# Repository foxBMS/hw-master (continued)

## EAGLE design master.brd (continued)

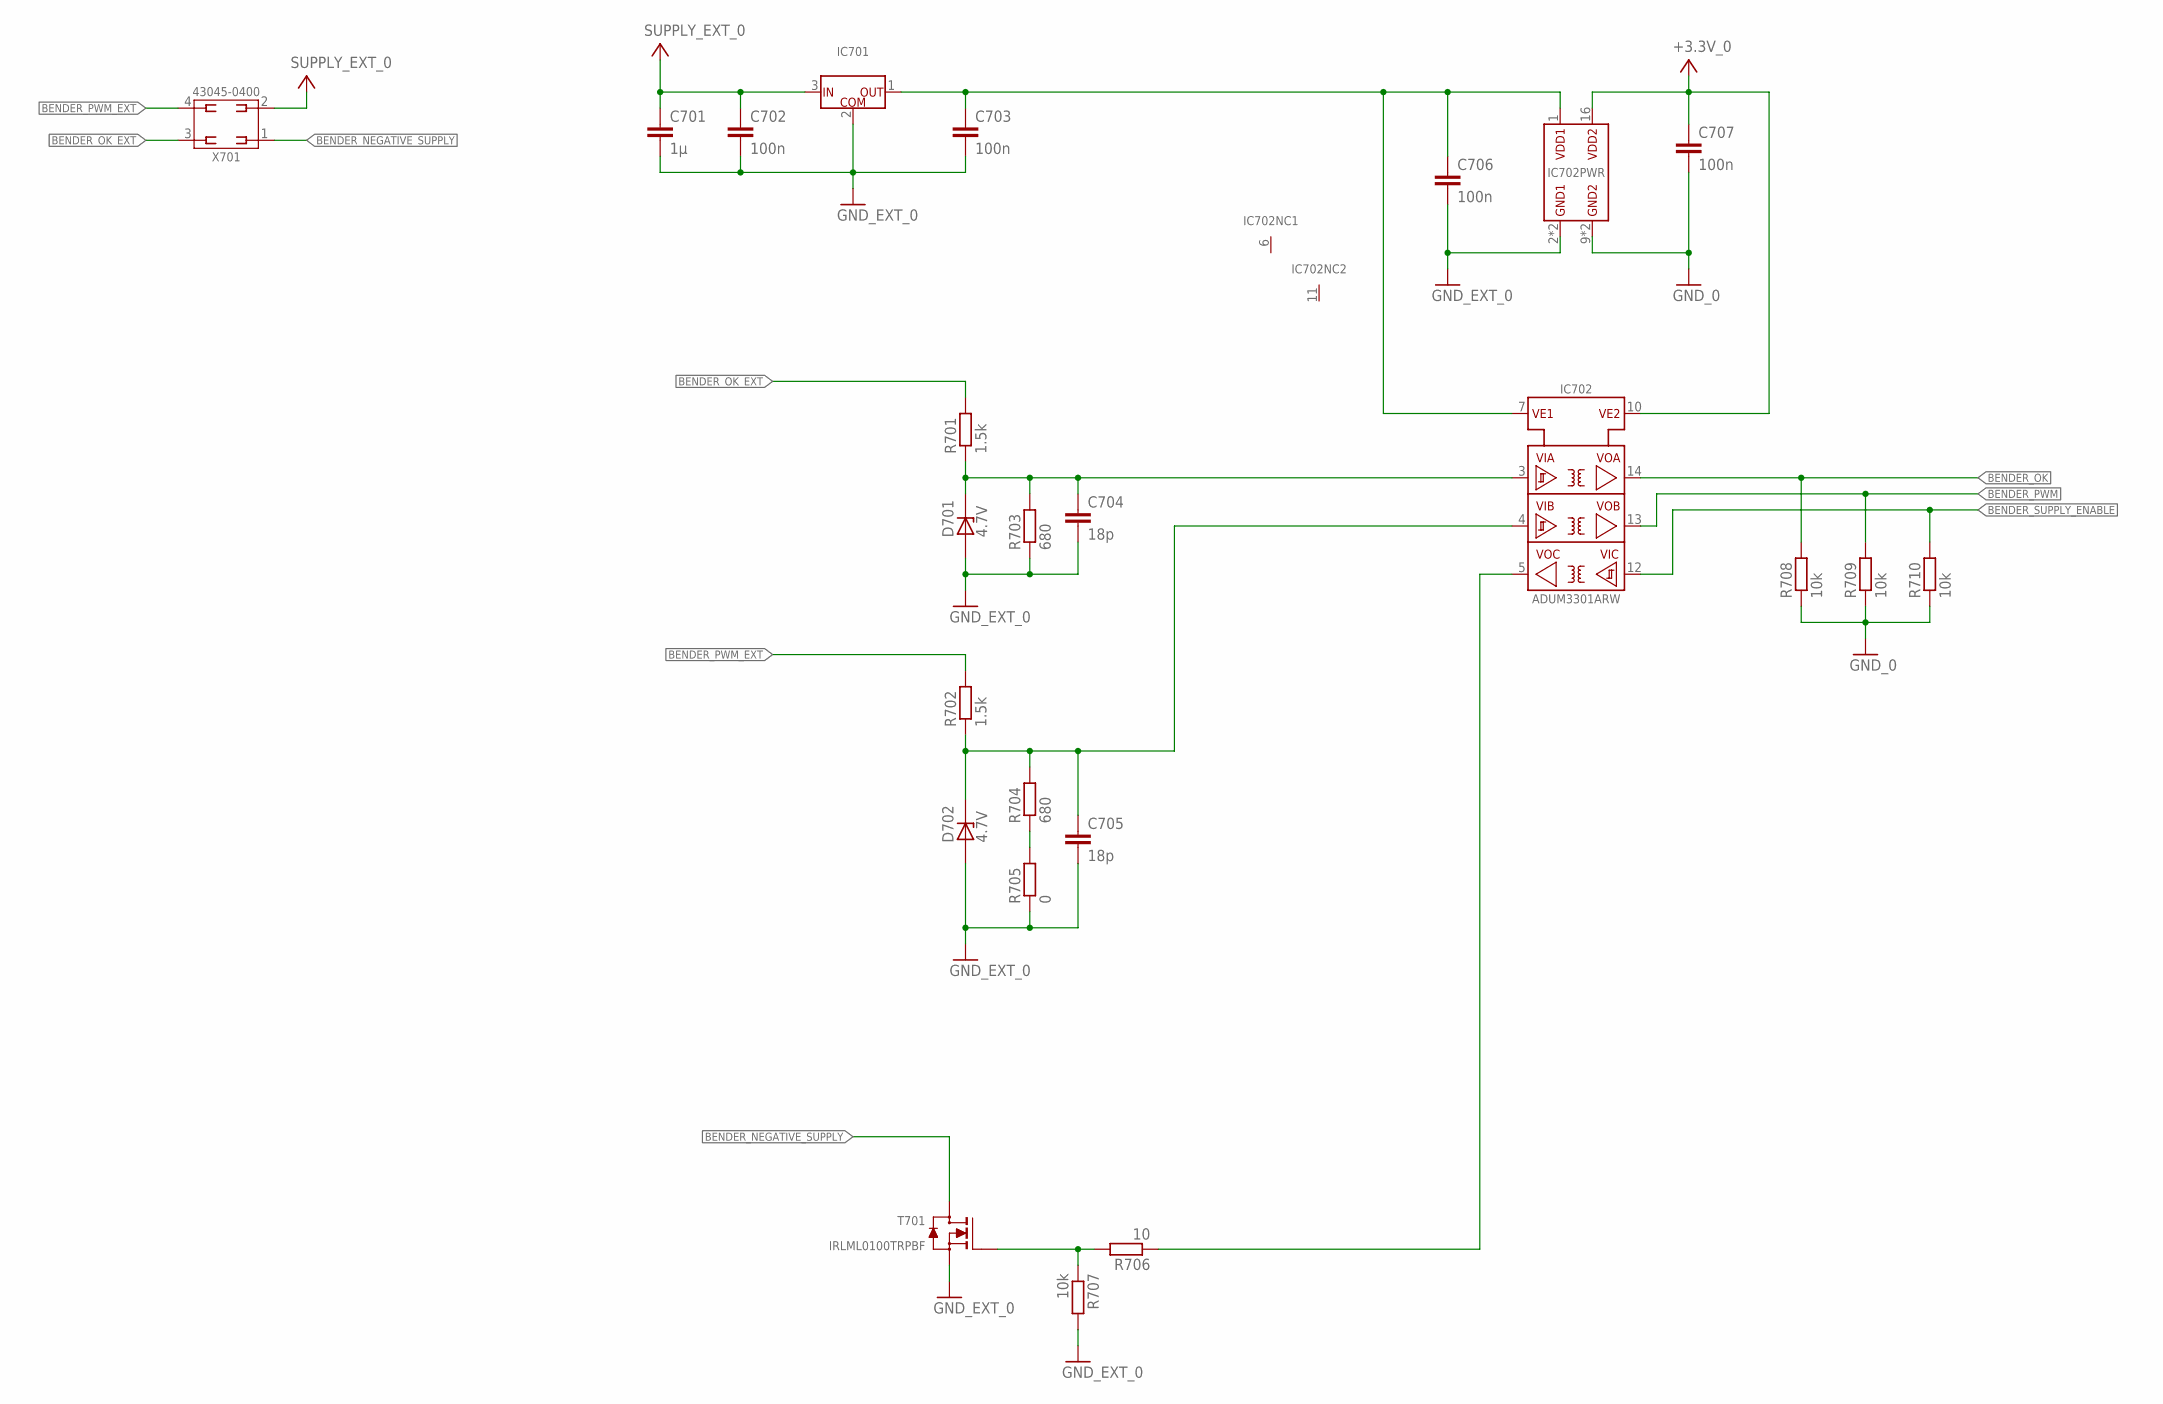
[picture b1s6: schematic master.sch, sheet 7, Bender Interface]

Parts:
C701: 1µ; C0603
C702, C703, C706, C707: 100n; C0603
C704, C705: 18p; C0603
D701, D702: 4.7V; SOD323
IC701: UA78L05ACPK; IC_SMD_SOT-89_(SC-62/TO-243)_(R-PSSO-F3)_R_TI_REV01
IC702: ADUM3301ARW; IC_SMD_SOIC-16_(JEDEC_MS-013-AA)_R_ANALOG_REV01
R701, R702: 1.5k; R0603
R703, R704: 680; R0603
R705: 0; R0603
R706: 10; R0603
R707, R708, R709, R710: 10k; R0603
T701: IRLML0100TRPBF; V_SMD_SOT-23_(TO-236AB)_R_IR_REV01
X701: 43045-0400_MOLEX_4PIN; X_TH_MOLEX_43045-0400_R_REV01

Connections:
+3.3V_0: C707.1, IC702.10 (VE2), IC702.16 (VDD2); also elsewhere on the board
BENDER_ADUM_SUPPLY: C703.1, C706.1, IC701.1 (OUT), IC702.1 (VDD1), IC702.7 (VE1)
BENDER_NEGATIVE_SUPPLY: T701.3 (D), X701.1
BENDER_OK: IC702.14 (VOA), R708.2; also elsewhere on the board
BENDER_OK_EXT: R701.2, X701.3
BENDER_PWM: IC702.13 (VOB), R709.2; also elsewhere on the board
BENDER_PWM_EXT: R702.2, X701.4
BENDER_SUPPLY_ENABLE: IC702.12 (VIC), R710.2; also elsewhere on the board
GND_0: C707.2, IC702.9 (GND2), IC702.15 (GND2), R708.1, R709.1, R710.1; also elsewhere on the board
GND_EXT_0: C701.2, C702.2, C703.2, C704.2, C705.2, C706.2, D701.A, D702.A, IC701.2 (COM), IC702.2 (GND1), IC702.8 (GND1), R703.1, R705.1, R707.2, T701.2 (S); also elsewhere on the board
unnamed: IC702.5 (VOC), R706.1
unnamed: R706.2, R707.1, T701.1 (G)
unnamed: C705.1, D702.C (K), IC702.4 (VIB), R702.1, R704.2
unnamed: C704.1, D701.C (K), IC702.3 (VIA), R701.1, R703.2
unnamed: R704.1, R705.2
SUPPLY_EXT_0: C701.1, C702.1, IC701.3 (IN), X701.2; also elsewhere on the board

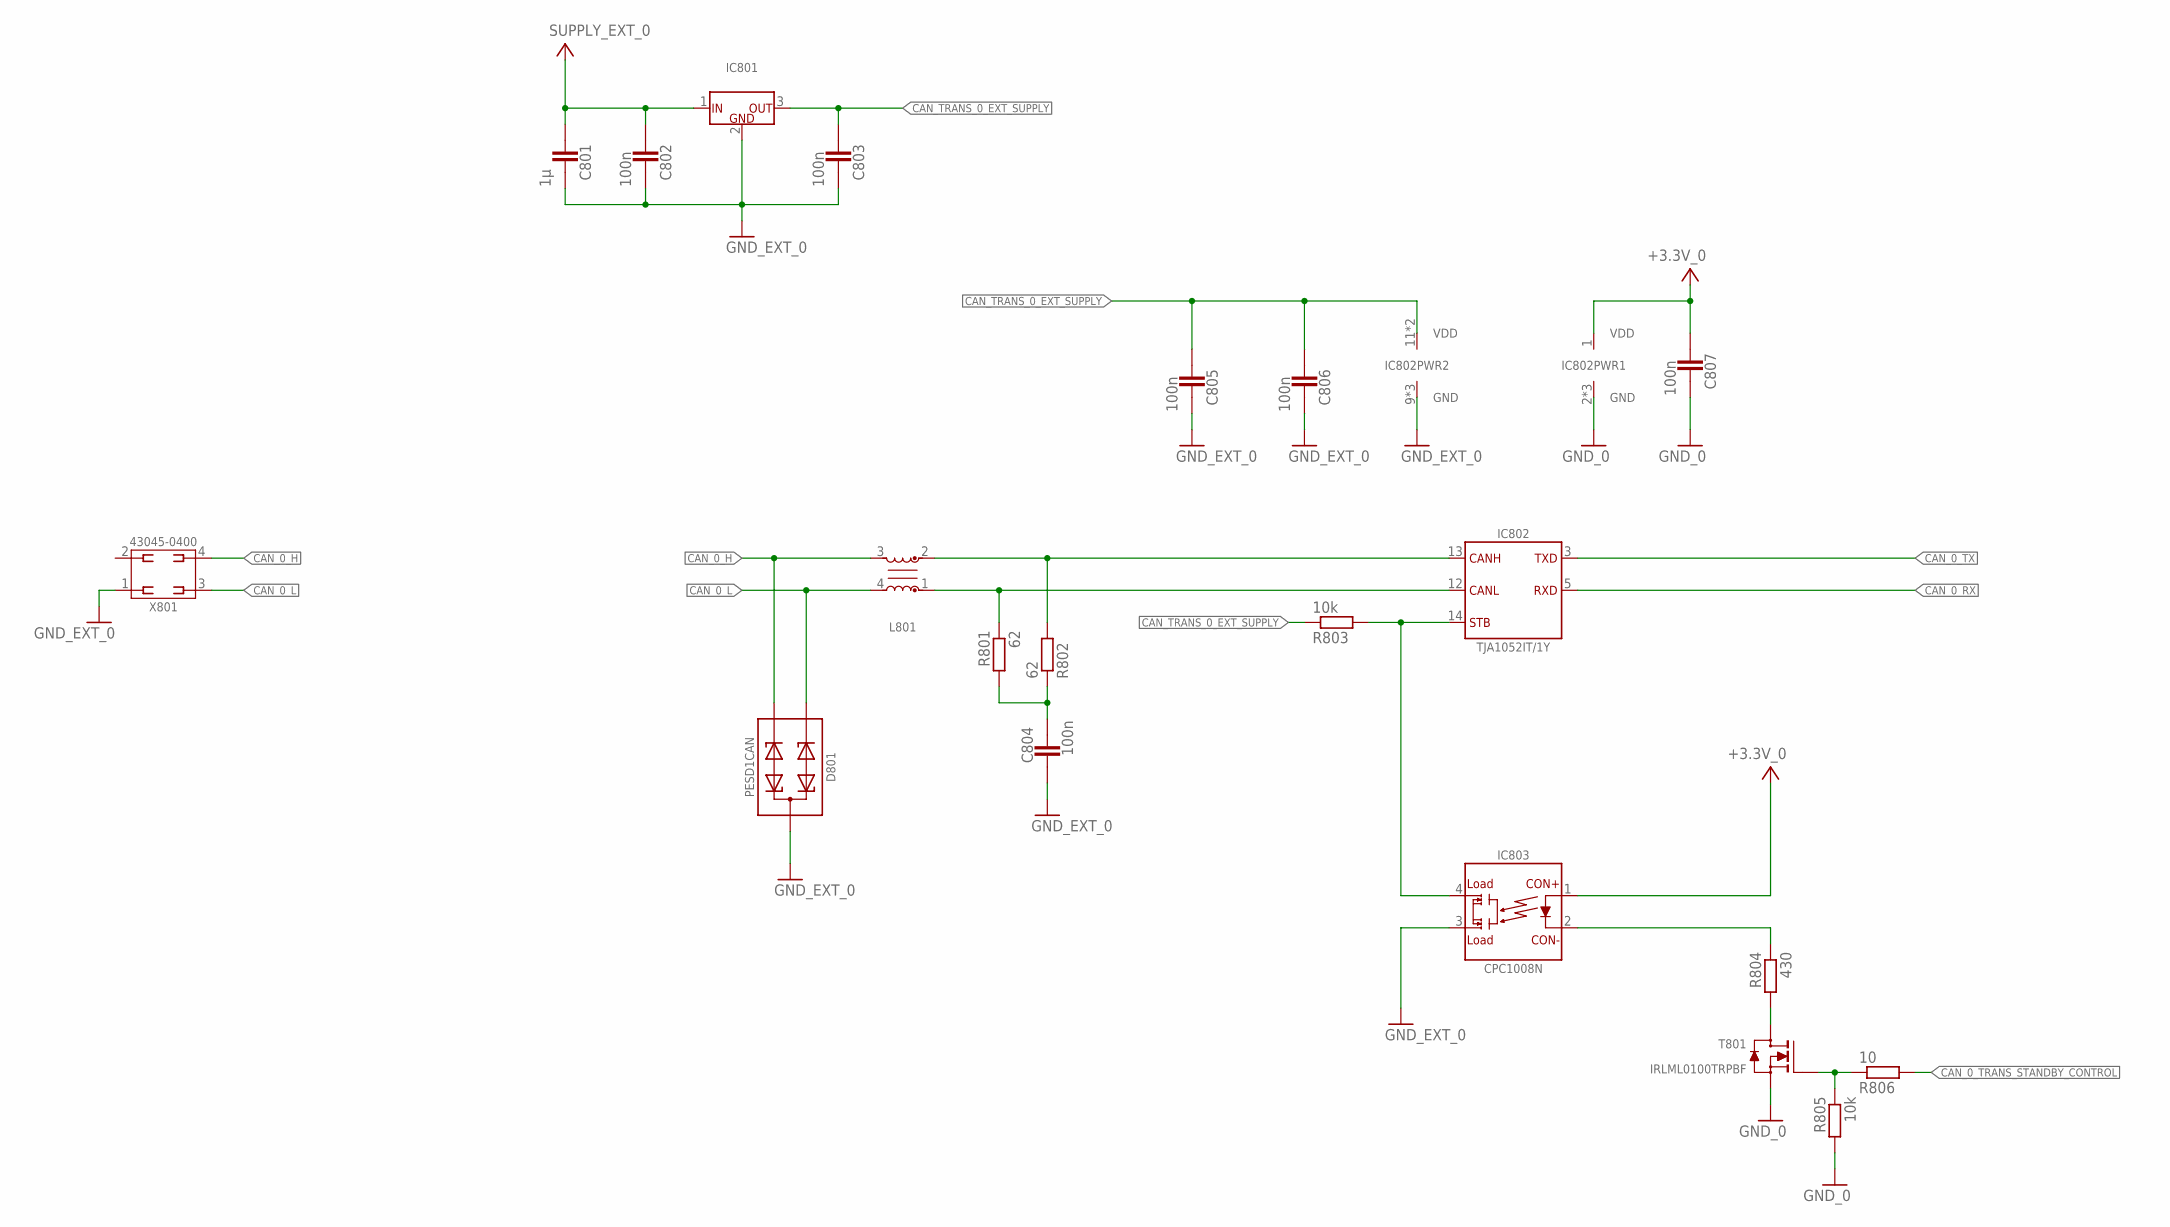
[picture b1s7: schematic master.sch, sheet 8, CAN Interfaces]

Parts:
C801: 1µ; 0603
C802, C803, C804, C805, C806, C807: 100n; 0603
D801: PESD1CAN; D_SMD_SOT23_(TO-236AB)_R_NXP_REV01
IC801: KA7805ERTF; IC_SMD_TO-252_(D-PAK)_R_FAIRCHILD_REV01
IC802: TJA1052IT/1Y; IC_SMD_SO16_(SOT162-1)_R_NXP_REV01
IC803: CPC1008N; K_SMD_SOP-4_R_IXYS_REV01
L801: B82789C0513H001; L_SMD_FILTER_HF_R_EPCOS_SIMDAD_1812_REV01
R801, R802: 62; R0603
R803, R805: 10k; 0603
R804: 430; 0603
R806: 10; 0603
T801: IRLML0100TRPBF; V_SMD_SOT-23_(TO-236AB)_R_IR_REV01
X801: 43045-0400_MOLEX_4PIN; X_TH_MOLEX_43045-0400_R_REV01

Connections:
+3.3V_0: C807.2, IC802.1 (VDD), IC803.1 (CON+); also elsewhere on the board
CAN_0_H: D801.2, L801.3, X801.4
CAN_0_L: D801.1, L801.4, X801.3
CAN_0_RX: IC802.5 (RXD); also elsewhere on the board
CAN_0_TRANS_STANDBY_CONTROL: R806.2; also elsewhere on the board
CAN_0_TX: IC802.3 (TXD); also elsewhere on the board
CAN_L_INT: IC802.12 (CANL), L801.1, R801.1
CAN_SPLIT: C804.1, R801.2, R802.1
CAN_TRANS_0_EXT_SUPPLY: C803.2, C805.2, C806.2, IC801.3 (OUT), IC802.11 (VDD), IC802.16 (VDD), R803.1
CAN_TRANS_0_STANDBY: IC802.14 (STB), IC803.4, R803.2
GND_0: C807.1, IC802.2 (GND), IC802.7 (GND), IC802.8 (GND), R805.2, T801.2 (S); also elsewhere on the board
GND_EXT_0: C801.1, C802.1, C803.1, C804.2, C805.1, C806.1, D801.3, IC801.2 (GND), IC802.9 (GND), IC802.10 (GND), IC802.15 (GND), IC803.3, X801.1; also elsewhere on the board
unnamed: R804.2, T801.3 (D)
unnamed: IC802.13 (CANH), L801.2, R802.2
unnamed: IC803.2 (CON-), R804.1
unnamed: R805.1, R806.1, T801.1 (G)
SUPPLY_EXT_0: C801.2, C802.2, IC801.1 (IN); also elsewhere on the board

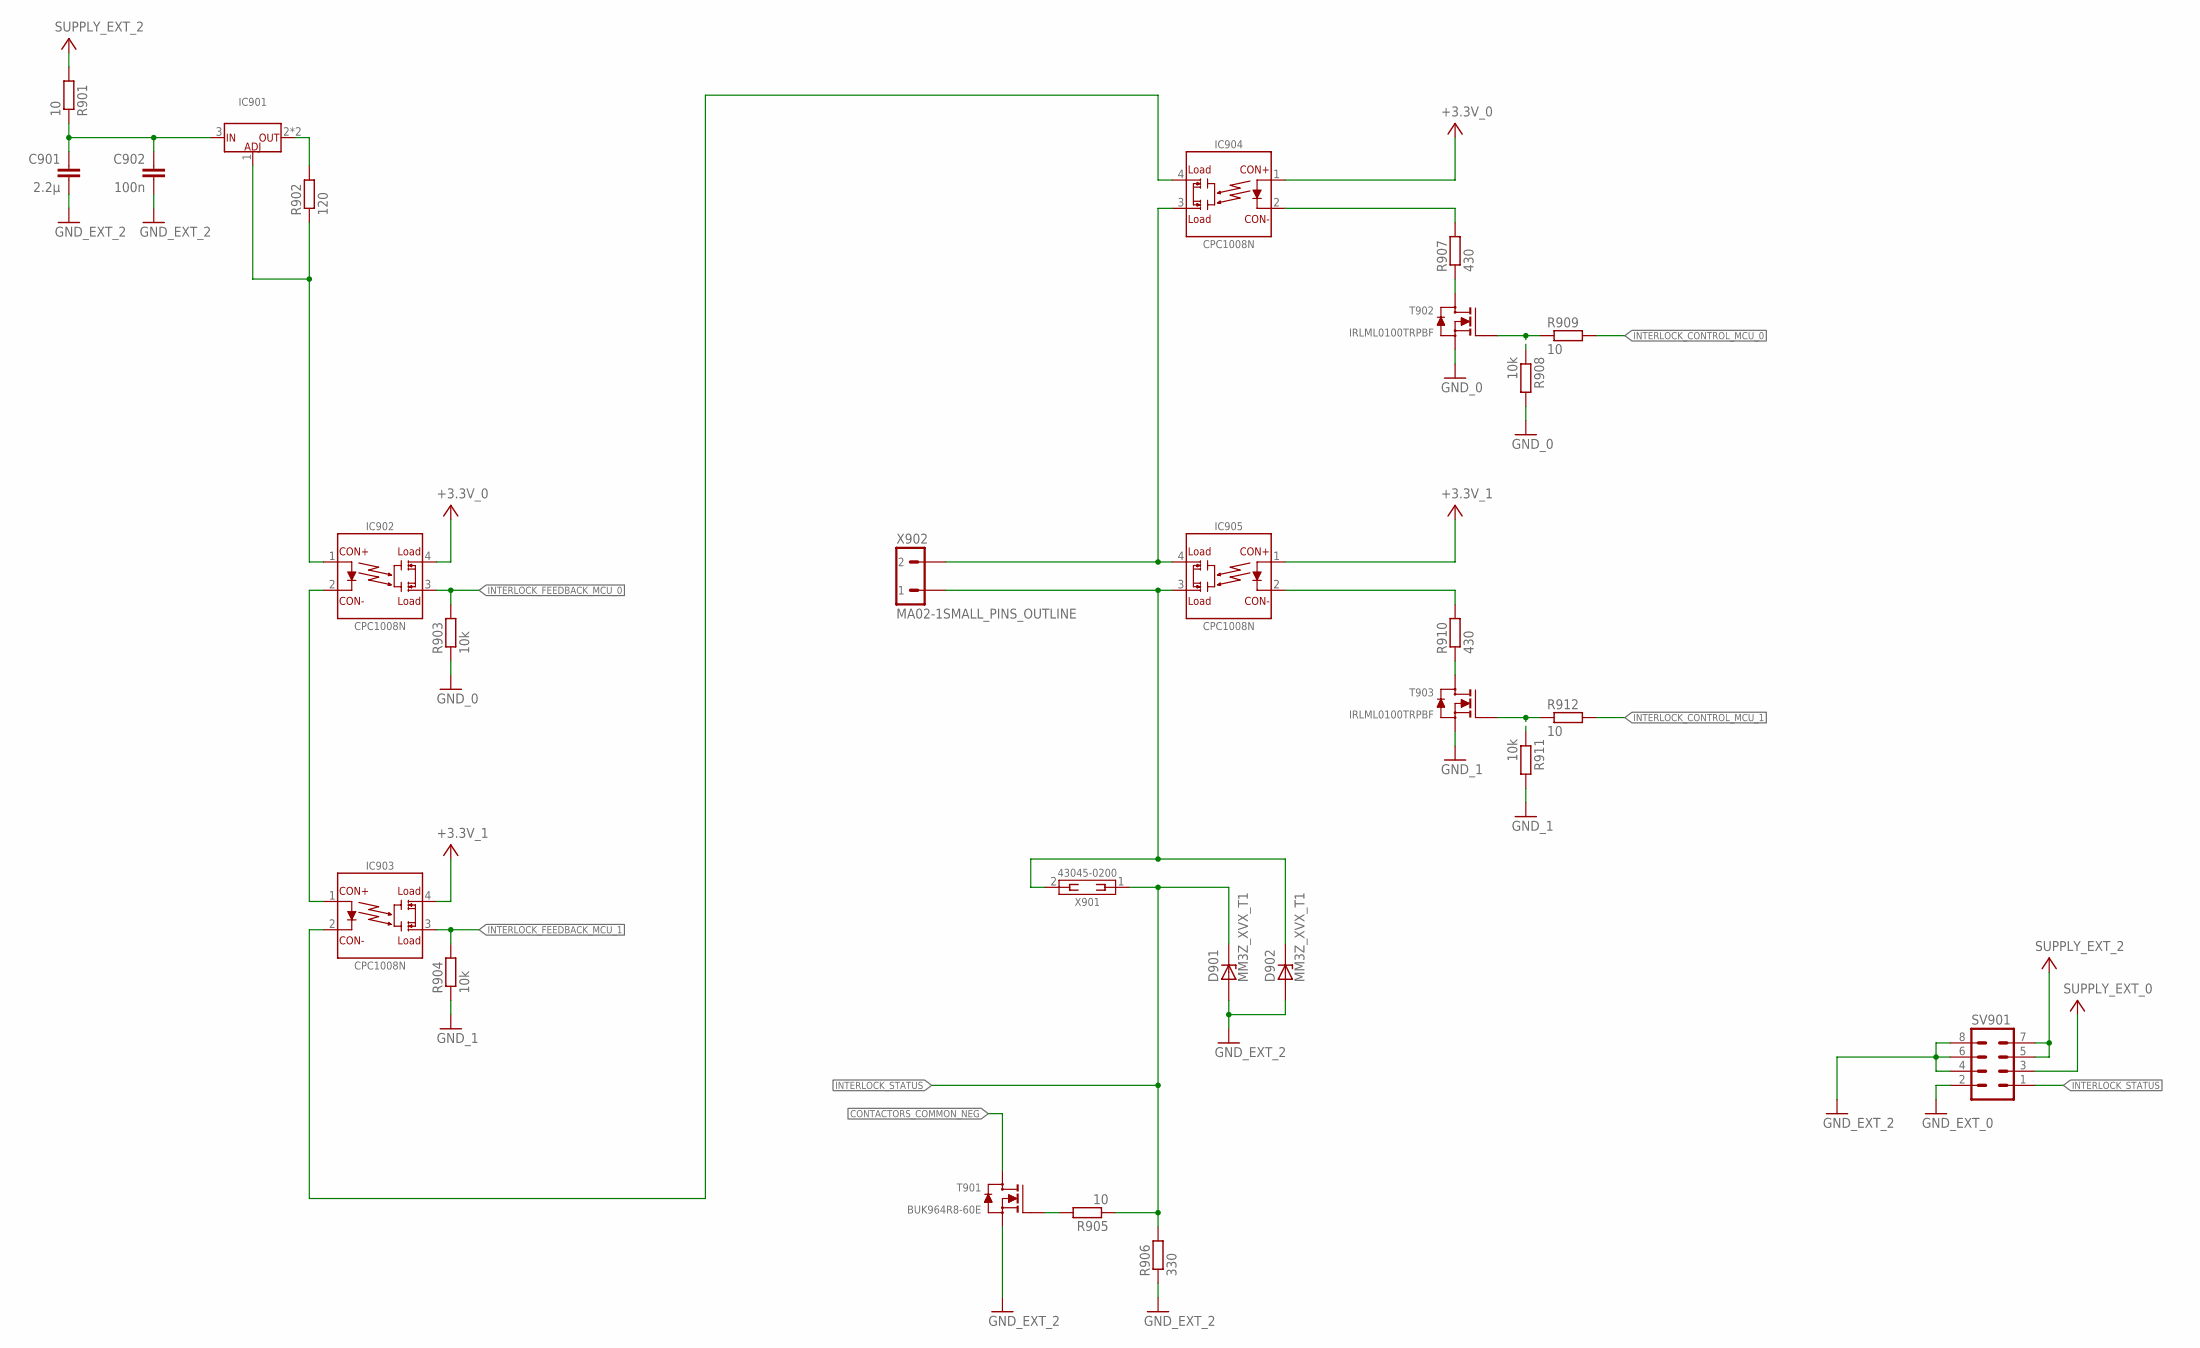
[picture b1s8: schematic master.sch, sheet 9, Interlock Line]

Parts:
C901: 2.2µ; C0805
C902: 100n; C0603
D901, D902: MM3Z_XVX_T1; SOD323
IC901: LM317MBSTT3G; IC_SMD_SOT-223_(TO-261)_(CASE318E-04)_R_REV01
IC902, IC903, IC904, IC905: CPC1008N; K_SMD_SOP-4_R_IXYS_REV01
R901, R905, R909, R912: 10; R0603
R902: 120; R0603
R903, R904, R908, R911: 10k; R0603
R906: 330; R0603
R907, R910: 430; R0603
SV901: MA04-2
T901: BUK964R8-60E; V_SMD_TO-263_(D²PAK)_R_NXP_REV01
T902, T903: IRLML0100TRPBF; V_SMD_SOT-23_(TO-236AB)_R_IR_REV01
X901: 43045-0200_MOLEX_2PIN; X_TH_MOLEX_43045-0200_R_REV01
X902: MA02-1SMALL_PINS_OUTLINE; MA02-1A

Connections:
+3.3V_0: IC902.4, IC904.1 (CON+); also elsewhere on the board
+3.3V_1: IC903.4, IC905.1 (CON+); also elsewhere on the board
CONTACTORS_COMMON_NEG: T901.2 (D); also elsewhere on the board
GND_0: R903.1, R908.2, T902.2 (S); also elsewhere on the board
GND_1: R904.1, R911.2, T903.2 (S); also elsewhere on the board
GND_EXT_0: SV901.2; also elsewhere on the board
GND_EXT_2: C901.2, C902.2, D901.A, D902.A, R906.1, SV901.4, SV901.6, SV901.8, T901.3 (S); also elsewhere on the board
INTERLOCK_CONTROL_MCU_0: R909.2; also elsewhere on the board
INTERLOCK_CONTROL_MCU_1: R912.2; also elsewhere on the board
INTERLOCK_FEEDBACK_MCU_0: IC902.3, R903.2; also elsewhere on the board
INTERLOCK_FEEDBACK_MCU_1: IC903.3, R904.2; also elsewhere on the board
INTERLOCK_STATUS: D901.C (K), R905.1, R906.2, SV901.1, X901.1
unnamed: R905.2, T901.1 (G)
unnamed: D902.C (K), IC905.3, X901.2, X902.1
unnamed: R907.1, T902.3 (D)
unnamed: R910.1, T903.3 (D)
unnamed: C901.1, C902.1, IC901.3 (IN), R901.1
unnamed: IC901.2 (OUT), IC901.4 (OUT), R902.2
unnamed: IC901.1 (ADJ), IC902.1 (CON+), R902.1
unnamed: IC902.2 (CON-), IC903.1 (CON+)
unnamed: IC905.2 (CON-), R910.2
unnamed: R911.1, R912.1, T903.1 (G)
unnamed: IC903.2 (CON-), IC904.4
unnamed: IC904.2 (CON-), R907.2
unnamed: R908.1, R909.1, T902.1 (G)
unnamed: IC904.3, IC905.4, X902.2
SUPPLY_EXT_0: SV901.3; also elsewhere on the board
SUPPLY_EXT_2: R901.2, SV901.5, SV901.7; also elsewhere on the board

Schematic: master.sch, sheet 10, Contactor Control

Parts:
D1001, D1002, D1003, D1004, D1005, D1006: GF1; SMA-DO214AC
F1001, F1002, F1003, F1004, F1005, F1006: 4,00A_UMT; F_SMD_11,00MMX3,00MMX3,00MM_(UMT)_R_SCHURTER_REV01
IC1001, IC1002, IC1003, IC1004, IC1005, IC1006: AQV252G2S; K_SMD_SOP-6_R_PANASONIC_REV01
R1001, R1002, R1007, R1008, R1013, R1014: 10; R0603
R1003, R1004, R1009, R1010, R1015, R1016: 10k; R0603
R1005, R1006, R1011, R1012, R1017, R1018: 430; R0603
T1001, T1002, T1003, T1004, T1005, T1006: IRLML0100TRPBF; V_SMD_SOT-23_(TO-236AB)_R_IR_REV01

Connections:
+3.3V_0: IC1001.1, IC1002.1, IC1003.1, IC1004.1, IC1005.1, IC1006.1; also elsewhere on the board
CONTACTORS_COMMON_NEG: D1001.A, D1002.A, D1003.A, D1004.A, D1005.A, D1006.A; also elsewhere on the board
CONTACTOR_0_COIL_POS: D1001.K (C), F1001.2; also elsewhere on the board
CONTACTOR_0_CONTROL: R1001.2; also elsewhere on the board
CONTACTOR_1_COIL_POS: D1003.K (C), F1003.2; also elsewhere on the board
CONTACTOR_1_CONTROL: R1007.2; also elsewhere on the board
CONTACTOR_2_COIL_POS: D1005.K (C), F1005.2; also elsewhere on the board
CONTACTOR_2_CONTROL: R1013.2; also elsewhere on the board
CONTACTOR_3_COIL_POS: D1002.K (C), F1002.2; also elsewhere on the board
CONTACTOR_3_CONTROL: R1002.2; also elsewhere on the board
CONTACTOR_4_COIL_POS: D1004.K (C), F1004.2; also elsewhere on the board
CONTACTOR_4_CONTROL: R1008.2; also elsewhere on the board
CONTACTOR_5_COIL_POS: D1006.K (C), F1006.2; also elsewhere on the board
CONTACTOR_5_CONTROL: R1014.2; also elsewhere on the board
GND_0: R1003.1, R1004.1, R1009.1, R1010.1, R1015.1, R1016.1, T1001.2 (S), T1002.2 (S), T1003.2 (S), T1004.2 (S), T1005.2 (S), T1006.2 (S); also elsewhere on the board
unnamed: IC1002.2, R1006.2
unnamed: R1006.1, T1002.3 (D)
unnamed: IC1001.2, R1005.2
unnamed: R1005.1, T1001.3 (D)
unnamed: R1011.1, T1003.3 (D)
unnamed: IC1003.2, R1011.2
unnamed: IC1004.2, R1012.2
unnamed: R1012.1, T1004.3 (D)
unnamed: IC1005.2, R1017.2
unnamed: R1017.1, T1005.3 (D)
unnamed: IC1006.2, R1018.2
unnamed: R1018.1, T1006.3 (D)
unnamed: F1001.1, IC1001.5
unnamed: F1003.1, IC1003.5
unnamed: F1004.1, IC1004.5
unnamed: F1005.1, IC1005.5
unnamed: F1002.1, IC1002.5
unnamed: F1006.1, IC1006.5
unnamed: R1007.1, R1009.2, T1003.1 (G)
unnamed: R1001.1, R1003.2, T1001.1 (G)
unnamed: R1013.1, R1015.2, T1005.1 (G)
unnamed: R1002.1, R1004.2, T1002.1 (G)
unnamed: R1008.1, R1010.2, T1004.1 (G)
unnamed: R1014.1, R1016.2, T1006.1 (G)
SUPPLY_EXT_2: IC1001.4, IC1001.6, IC1002.4, IC1002.6, IC1003.4, IC1003.6, IC1004.4, IC1004.6, IC1005.4, IC1005.6, IC1006.4, IC1006.6; also elsewhere on the board

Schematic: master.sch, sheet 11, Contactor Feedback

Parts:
C1101: 1µ; C0603
C1102, C1103, C1104, C1105, C1106, C1107: 100n; C0603
D1101, D1102, D1103, D1104, D1105, D1106: CDSOD323-T05; D_SMD_SOD323_(SC-76)_R_BOURNS_REV01
IC1101: UA78L05ACPK; IC_SMD_SOT-89_(SC-62/TO-243)_(R-PSSO-F3)_R_TI_REV01
IC1102, IC1103: ADUM3300ARW; IC_SMD_SOIC-16_(JEDEC_MS-013-AA)_R_ANALOG_REV01
R1101, R1102, R1103, R1104, R1105, R1106: 47; R0603
R1107, R1108, R1109, R1110, R1111, R1112: 10k; R0603

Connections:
+3.3V_0: C1106.1, C1107.1, IC1102.10 (VE2), IC1102.16 (VDD2), IC1103.10 (VE2), IC1103.16 (VDD2); also elsewhere on the board
CONTACTOR_0_FEEDBACK: IC1102.14 (VOA); also elsewhere on the board
CONTACTOR_0_FEEDBACK_EXT: R1101.1; also elsewhere on the board
CONTACTOR_1_FEEDBACK: IC1102.13 (VOB); also elsewhere on the board
CONTACTOR_1_FEEDBACK_EXT: R1102.1; also elsewhere on the board
CONTACTOR_2_FEEDBACK: IC1102.12 (VOC); also elsewhere on the board
CONTACTOR_2_FEEDBACK_EXT: R1103.1; also elsewhere on the board
CONTACTOR_3_FEEDBACK: IC1103.14 (VOA); also elsewhere on the board
CONTACTOR_3_FEEDBACK_EXT: R1104.2; also elsewhere on the board
CONTACTOR_4_FEEDBACK: IC1103.13 (VOB); also elsewhere on the board
CONTACTOR_4_FEEDBACK_EXT: R1105.2; also elsewhere on the board
CONTACTOR_5_FEEDBACK: IC1103.12 (VOC); also elsewhere on the board
CONTACTOR_5_FEEDBACK_EXT: R1106.2; also elsewhere on the board
CONTACTOR_FEEDBACK_SUPPLY_EXT: C1103.1, C1104.1, C1105.1, IC1101.1 (OUT), IC1102.1 (VDD1), IC1103.1 (VDD1), R1107.2, R1108.2, R1109.2, R1110.2, R1111.2, R1112.2
GND_0: C1106.2, C1107.2, IC1102.9 (GND2), IC1102.15 (GND2), IC1103.9 (GND2), IC1103.15 (GND2); also elsewhere on the board
GND_EXT_0: C1101.2, C1102.2, C1103.2, C1104.2, C1105.2, D1101.A, D1102.A, D1103.A, D1104.A, D1105.A, D1106.A, IC1101.2 (COM), IC1102.2 (GND1), IC1102.8 (GND1), IC1103.2 (GND1), IC1103.8 (GND1); also elsewhere on the board
unnamed: D1101.C, IC1102.3 (VIA), R1101.2, R1107.1
unnamed: D1103.C, IC1102.4 (VIB), R1102.2, R1109.1
unnamed: D1105.C, IC1102.5 (VIC), R1103.2, R1111.1
unnamed: D1102.C, IC1103.3 (VIA), R1104.1, R1108.1
unnamed: D1104.C, IC1103.4 (VIB), R1105.1, R1110.1
unnamed: D1106.C, IC1103.5 (VIC), R1106.1, R1112.1
SUPPLY_EXT_0: C1101.1, C1102.1, IC1101.3 (IN); also elsewhere on the board

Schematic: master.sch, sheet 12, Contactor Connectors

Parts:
X1201, X1202, X1203, X1204, X1205, X1206: 43045-0400_MOLEX_4PIN; X_TH_MOLEX_43045-0400_R_REV01

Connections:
CONTACTORS_COMMON_NEG: X1201.4, X1202.4, X1203.4, X1204.4, X1205.4, X1206.4; also elsewhere on the board
CONTACTOR_0_COIL_POS: X1201.3; also elsewhere on the board
CONTACTOR_0_FEEDBACK_EXT: X1201.2; also elsewhere on the board
CONTACTOR_1_COIL_POS: X1203.3; also elsewhere on the board
CONTACTOR_1_FEEDBACK_EXT: X1203.2; also elsewhere on the board
CONTACTOR_2_COIL_POS: X1205.3; also elsewhere on the board
CONTACTOR_2_FEEDBACK_EXT: X1205.2; also elsewhere on the board
CONTACTOR_3_COIL_POS: X1202.3; also elsewhere on the board
CONTACTOR_3_FEEDBACK_EXT: X1202.2; also elsewhere on the board
CONTACTOR_4_COIL_POS: X1204.3; also elsewhere on the board
CONTACTOR_4_FEEDBACK_EXT: X1204.2; also elsewhere on the board
CONTACTOR_5_COIL_POS: X1206.3; also elsewhere on the board
CONTACTOR_5_FEEDBACK_EXT: X1206.2; also elsewhere on the board
GND_EXT_0: X1201.1, X1202.1, X1203.1, X1204.1, X1205.1, X1206.1; also elsewhere on the board

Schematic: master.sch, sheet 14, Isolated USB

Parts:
C1401, C1406: 4.7µ; C0603
C1402, C1403, C1404, C1405, C1407, C1408, C1409, C1410: 100n; C0603
IC1401, IC1404: IP4220CZ6; D_SMD_TSOP6_(SOT457/SC-74)_R_NXP_REV01
IC1402, IC1405: FT231XS-R; IC_SMD_SSOP-20_R_FTDI_REV01
IC1403, IC1406: ADUM3401ARW; IC_SMD_SOIC-16_(JEDEC_MS-013-AA)_R_ANALOG_REV01
R1401, R1402, R1405, R1406: 27; 0603
R1403, R1404, R1407, R1408: 0; 0603
X1401, X1402: MINI-USB-2.0; X_SMD_MINI-USB-2.0-TYPAB_R_MULTICOMP_REV01

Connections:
+3.3V_0: C1405.1, IC1403.10 (VE2), IC1403.16 (VDD2); also elsewhere on the board
+3.3V_1: C1410.1, IC1406.10 (VE2), IC1406.16 (VDD2); also elsewhere on the board
DM: IC1401.4 (I/O3), R1401.2, X1401.2
DM1: IC1404.4 (I/O3), R1405.2, X1402.2
DP: IC1401.6 (I/O4), R1402.2, X1401.3
DP1: IC1404.6 (I/O4), R1406.2, X1402.3
FTDI_MCU_0_DTR: IC1403.13 (VOB); also elsewhere on the board
FTDI_MCU_0_RTS: IC1403.14 (VOA); also elsewhere on the board
FTDI_MCU_0_RX: IC1403.12 (VOC); also elsewhere on the board
FTDI_MCU_0_TX: IC1403.11 (VID); also elsewhere on the board
FTDI_MCU_1_DTR: IC1406.13 (VOB); also elsewhere on the board
FTDI_MCU_1_RTS: IC1406.14 (VOA); also elsewhere on the board
FTDI_MCU_1_RX: IC1406.12 (VOC); also elsewhere on the board
FTDI_MCU_1_TX: IC1406.11 (VID); also elsewhere on the board
GND_0: C1405.2, IC1403.9 (GND2), IC1403.15 (GND2); also elsewhere on the board
GND_1: C1410.2, IC1406.9 (GND2), IC1406.15 (GND2); also elsewhere on the board
unnamed: IC1402.11 (USBDP), R1402.1
unnamed: IC1402.12 (USBDM), R1401.1
unnamed: IC1405.11 (USBDP), R1406.1
unnamed: IC1405.12 (USBDM), R1405.1
unnamed: IC1402.20 (TXD), IC1403.5 (VIC)
unnamed: IC1405.20 (TXD), IC1406.5 (VIC)
unnamed: IC1405.4 (RXD), IC1406.6 (VOD)
unnamed: IC1405.2 (RTS#), IC1406.3 (VIA)
unnamed: IC1405.1 (DTR#), IC1406.4 (VIB)
unnamed: IC1402.4 (RXD), IC1403.6 (VOD)
unnamed: IC1402.1 (DTR#), IC1403.4 (VIB)
unnamed: C1409.1, IC1405.3 (VCCIO), IC1405.13 (3V3OUT), IC1405.14 (RESET#)
unnamed: IC1405.9 (CTS#), R1407.1
unnamed: IC1402.2 (RTS#), IC1403.3 (VIA)
unnamed: IC1405.7 (DSR#), R1408.1
unnamed: IC1402.9 (CTS#), R1403.1
unnamed: IC1402.7 (DSR#), R1404.1
USB_0_GND_EXT: C1401.2, C1402.2, C1403.2, C1404.2, IC1401.2 (GND), IC1402.6 (GND1), IC1402.16 (GND2), IC1403.2 (GND1), IC1403.8 (GND1), R1403.2, R1404.2, X1401.5
USB_0_VBUS1_EXT: C1401.1, C1402.1, C1403.1, IC1401.5 (VP), IC1402.15 (VCC), IC1403.1 (VDD1), IC1403.7 (VE1), X1401.1
USB_0_VCC_EXT: C1404.1, IC1402.3 (VCCIO), IC1402.13 (3V3OUT), IC1402.14 (RESET#)
USB_GND_0_EXT1: C1406.2, C1407.2, C1408.2, C1409.2, IC1404.2 (GND), IC1405.6 (GND1), IC1405.16 (GND2), IC1406.2 (GND1), IC1406.8 (GND1), R1407.2, R1408.2, X1402.5
USB_VBUS1_0_EXT1: C1406.1, C1407.1, C1408.1, IC1404.5 (VP), IC1405.15 (VCC), IC1406.1 (VDD1), IC1406.7 (VE1), X1402.1

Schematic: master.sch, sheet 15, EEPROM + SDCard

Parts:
C1501: 100n; 0603
IC1501: AT25128B-SSHL-T; IC_SMD_SOIC-8_R_ATMEL_REV01
R1501, R1502: 10k; 0603

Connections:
+3.3V_0: C1501.2, IC1501.8 (VCC), R1501.2, R1502.2; also elsewhere on the board
DATA_STORAGE_SPI_EEPROM_CS: IC1501.1 (!CS); also elsewhere on the board
DATA_STORAGE_SPI_MISO: IC1501.2 (SO); also elsewhere on the board
DATA_STORAGE_SPI_MOSI: IC1501.5 (SI); also elsewhere on the board
DATA_STORAGE_SPI_SCK: IC1501.6 (SCK); also elsewhere on the board
GND_0: C1501.1, IC1501.4 (GND); also elsewhere on the board
unnamed: IC1501.7 (HOLD), R1501.1
unnamed: IC1501.3 (!WP), R1502.1

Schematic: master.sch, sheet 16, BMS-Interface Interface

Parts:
C1601, C1602, C1603, C1604: 100n; C0603
SV1601, SV1603: MA04-2
SV1602, SV1604: MA08-2
X1601: 43045-1600_MOLEX_16PIN; X_TH_MOLEX_43045-1600_R_REV01

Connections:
+3.3V_0: C1601.1, SV1602.3; also elsewhere on the board
+3.3V_1: C1603.1, SV1604.3; also elsewhere on the board
+5.0V_0: C1602.1, SV1602.4; also elsewhere on the board
+5.0V_1: C1604.1, SV1604.4; also elsewhere on the board
BMS-INTERFACE_0_GPIO_0: SV1602.11; also elsewhere on the board
BMS-INTERFACE_0_GPIO_1: SV1602.12; also elsewhere on the board
BMS-INTERFACE_0_GPIO_2: SV1602.2; also elsewhere on the board
BMS-INTERFACE_0_GPIO_3: SV1602.1; also elsewhere on the board
BMS-INTERFACE_0_SPI_CS: SV1602.8; also elsewhere on the board
BMS-INTERFACE_0_SPI_MISO: SV1602.6; also elsewhere on the board
BMS-INTERFACE_0_SPI_MOSI: SV1602.5; also elsewhere on the board
BMS-INTERFACE_0_SPI_SCK: SV1602.7; also elsewhere on the board
BMS-INTERFACE_1_GPIO_0: SV1604.11; also elsewhere on the board
BMS-INTERFACE_1_GPIO_1: SV1604.12; also elsewhere on the board
BMS-INTERFACE_1_GPIO_2: SV1604.2; also elsewhere on the board
BMS-INTERFACE_1_GPIO_3: SV1604.1; also elsewhere on the board
BMS-INTERFACE_1_SPI_CS: SV1604.8; also elsewhere on the board
BMS-INTERFACE_1_SPI_MISO: SV1604.6; also elsewhere on the board
BMS-INTERFACE_1_SPI_MOSI: SV1604.5; also elsewhere on the board
BMS-INTERFACE_1_SPI_SCK: SV1604.7; also elsewhere on the board
GND_0: C1601.2, C1602.2, SV1602.9, SV1602.10; also elsewhere on the board
GND_1: C1603.2, C1604.2, SV1604.9, SV1604.10; also elsewhere on the board
unnamed: SV1601.1, X1601.1
unnamed: SV1601.2, X1601.9
unnamed: SV1601.3, X1601.2
unnamed: SV1601.4, X1601.10
unnamed: SV1601.5, X1601.3
unnamed: SV1601.6, X1601.11
unnamed: SV1601.7, X1601.4
unnamed: SV1601.8, X1601.12
unnamed: SV1603.1, X1601.5
unnamed: SV1603.3, X1601.6
unnamed: SV1603.5, X1601.7
unnamed: SV1603.7, X1601.8
unnamed: SV1603.2, X1601.13
unnamed: SV1603.4, X1601.14
unnamed: SV1603.6, X1601.15
unnamed: SV1603.8, X1601.16

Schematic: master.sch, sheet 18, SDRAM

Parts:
C1801, C1802, C1803, C1804, C1805, C1806, C1807: 100n; C0603
IC1801: IS42S16400J-5TL; IC_SMD_TSOP-II_(54-PIN)_R_ISSI_REV01

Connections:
+3.3V_0: C1801.1, C1802.1, C1803.1, C1804.1, C1805.1, C1806.1, C1807.1, IC1801.1 (VDD), IC1801.3 (VDDQ), IC1801.9 (VDDQ), IC1801.14 (VDD), IC1801.27 (VDD), IC1801.43 (VDDQ), IC1801.49 (VDDQ); also elsewhere on the board
FMC_MCU_0_RAM_A0: IC1801.23 (A0); also elsewhere on the board
FMC_MCU_0_RAM_A1: IC1801.24 (A1); also elsewhere on the board
FMC_MCU_0_RAM_A2: IC1801.25 (A2); also elsewhere on the board
FMC_MCU_0_RAM_A3: IC1801.26 (A3); also elsewhere on the board
FMC_MCU_0_RAM_A4: IC1801.29 (A4); also elsewhere on the board
FMC_MCU_0_RAM_A5: IC1801.30 (A5); also elsewhere on the board
FMC_MCU_0_RAM_A6: IC1801.31 (A6); also elsewhere on the board
FMC_MCU_0_RAM_A7: IC1801.32 (A7); also elsewhere on the board
FMC_MCU_0_RAM_A8: IC1801.33 (A8); also elsewhere on the board
FMC_MCU_0_RAM_A9: IC1801.34 (A9); also elsewhere on the board
FMC_MCU_0_RAM_A10: IC1801.22 (A10); also elsewhere on the board
FMC_MCU_0_RAM_A11: IC1801.35 (A11); also elsewhere on the board
FMC_MCU_0_RAM_BA0: IC1801.20 (BA0); also elsewhere on the board
FMC_MCU_0_RAM_BA1: IC1801.21 (BA1); also elsewhere on the board
FMC_MCU_0_RAM_D0: IC1801.2 (DQ0); also elsewhere on the board
FMC_MCU_0_RAM_D1: IC1801.4 (DQ1); also elsewhere on the board
FMC_MCU_0_RAM_D2: IC1801.5 (DQ2); also elsewhere on the board
FMC_MCU_0_RAM_D3: IC1801.7 (DQ3); also elsewhere on the board
FMC_MCU_0_RAM_D4: IC1801.8 (DQ4); also elsewhere on the board
FMC_MCU_0_RAM_D5: IC1801.10 (DQ5); also elsewhere on the board
FMC_MCU_0_RAM_D6: IC1801.11 (DQ6); also elsewhere on the board
FMC_MCU_0_RAM_D7: IC1801.13 (DQ7); also elsewhere on the board
FMC_MCU_0_RAM_D8: IC1801.42 (DQ8); also elsewhere on the board
FMC_MCU_0_RAM_D9: IC1801.44 (DQ9); also elsewhere on the board
FMC_MCU_0_RAM_D10: IC1801.45 (DQ10); also elsewhere on the board
FMC_MCU_0_RAM_D11: IC1801.47 (DQ11); also elsewhere on the board
FMC_MCU_0_RAM_D12: IC1801.48 (DQ12); also elsewhere on the board
FMC_MCU_0_RAM_D13: IC1801.50 (DQ13); also elsewhere on the board
FMC_MCU_0_RAM_D14: IC1801.51 (DQ14); also elsewhere on the board
FMC_MCU_0_RAM_D15: IC1801.53 (DQ15); also elsewhere on the board
FMC_MCU_0_RAM_NBL0: IC1801.15 (LDQM); also elsewhere on the board
FMC_MCU_0_RAM_NBL1: IC1801.39 (UDQM); also elsewhere on the board
FMC_MCU_0_RAM_SDCKE1: IC1801.37 (CKE); also elsewhere on the board
FMC_MCU_0_RAM_SDCLK: IC1801.38 (CLK); also elsewhere on the board
FMC_MCU_0_RAM_SDNCAS: IC1801.17 (!CAS); also elsewhere on the board
FMC_MCU_0_RAM_SDNE1: IC1801.19 (!CS); also elsewhere on the board
FMC_MCU_0_RAM_SDNRAS: IC1801.18 (!RAS); also elsewhere on the board
FMC_MCU_0_RAM_SDNWE: IC1801.16 (!WE); also elsewhere on the board
GND_0: C1801.2, C1802.2, C1803.2, C1804.2, C1805.2, C1806.2, C1807.2, IC1801.6 (GNDQ), IC1801.12 (GNDQ), IC1801.28 (GND), IC1801.41 (GND), IC1801.46 (GNDQ), IC1801.52 (GNDQ), IC1801.54 (GND); also elsewhere on the board

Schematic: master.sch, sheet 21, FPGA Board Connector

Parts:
C2101, C2102: 100n; C0603
SV2101: MA04-2

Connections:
+3.3V_0: C2101.2, SV2101.1; also elsewhere on the board
+5.0V_0: C2102.1, SV2101.2; also elsewhere on the board
GND_0: C2101.1, C2102.2, SV2101.5, SV2101.6; also elsewhere on the board
MCU_TO_FPGA_INTERFACE_MCU_0_CS: SV2101.8; also elsewhere on the board
MCU_TO_FPGA_INTERFACE_MCU_0_MISO: SV2101.3; also elsewhere on the board
MCU_TO_FPGA_INTERFACE_MCU_0_MOSI: SV2101.7; also elsewhere on the board
MCU_TO_FPGA_INTERFACE_MCU_0_SCK: SV2101.4; also elsewhere on the board

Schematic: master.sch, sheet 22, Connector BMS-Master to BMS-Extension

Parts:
JP2201, JP2202: PINHD-2X12; 2X12

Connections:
+3.3V_0: JP2201.1, JP2201.3, JP2202.1, JP2202.3; also elsewhere on the board
ADC_MCU_0_CH_0: JP2202.8; also elsewhere on the board
ADC_MCU_0_CH_1: JP2202.7; also elsewhere on the board
ADC_MCU_0_CH_2: JP2202.6; also elsewhere on the board
ADC_MCU_0_CH_3: JP2202.5; also elsewhere on the board
ADC_MCU_0_CH_4: JP2202.9; also elsewhere on the board
CAN_1_RX: JP2201.6; also elsewhere on the board
CAN_1_TRANS_STANDBY_CONTROL: JP2201.5; also elsewhere on the board
CAN_1_TX: JP2201.7; also elsewhere on the board
CONTACTOR_6_CONTROL: JP2201.18; also elsewhere on the board
CONTACTOR_6_FEEDBACK: JP2201.17; also elsewhere on the board
CONTACTOR_7_CONTROL: JP2201.16; also elsewhere on the board
CONTACTOR_7_FEEDBACK: JP2201.15; also elsewhere on the board
CONTACTOR_8_CONTROL: JP2202.10; also elsewhere on the board
CONTACTOR_8_FEEDBACK: JP2202.11; also elsewhere on the board
DATA_STORAGE_SPI_MISO: JP2201.21; also elsewhere on the board
DATA_STORAGE_SPI_MOSI: JP2201.19; also elsewhere on the board
DATA_STORAGE_SPI_SCK: JP2201.20; also elsewhere on the board
DATA_STORAGE_SPI_SDCARD_NSS: JP2201.23; also elsewhere on the board
GND_0: JP2201.2, JP2201.4, JP2202.2, JP2202.4; also elsewhere on the board
ISONOC_0_CONTROL: JP2202.16; also elsewhere on the board
ISONOC_1_CONTROL: JP2202.17; also elsewhere on the board
ISONOC_2_CONTROL: JP2202.18; also elsewhere on the board
ISONOC_3_CONTROL: JP2202.19; also elsewhere on the board
ISONOC_4_CONTROL: JP2202.20; also elsewhere on the board
ISONOC_5_CONTROL: JP2202.21; also elsewhere on the board
ISO_GPIO_MCU_0_IN_0: JP2202.22; also elsewhere on the board
ISO_GPIO_MCU_0_IN_1: JP2202.23; also elsewhere on the board
ISO_GPIO_MCU_0_IN_2: JP2201.13; also elsewhere on the board
ISO_GPIO_MCU_0_IN_3: JP2201.10; also elsewhere on the board
ISO_GPIO_MCU_0_OUT_0: JP2201.9; also elsewhere on the board
ISO_GPIO_MCU_0_OUT_1: JP2201.14; also elsewhere on the board
ISO_GPIO_MCU_0_OUT_2: JP2201.11; also elsewhere on the board
ISO_GPIO_MCU_0_OUT_3: JP2201.12; also elsewhere on the board
RS485_MCU_0_DE: JP2202.15; also elsewhere on the board
RS485_MCU_0_NRE: JP2202.14; also elsewhere on the board
RS485_MCU_0_RX: JP2202.13; also elsewhere on the board
RS485_MCU_0_TX: JP2202.12; also elsewhere on the board
SDCARD_SUPPLY_CONTROL: JP2201.22; also elsewhere on the board
